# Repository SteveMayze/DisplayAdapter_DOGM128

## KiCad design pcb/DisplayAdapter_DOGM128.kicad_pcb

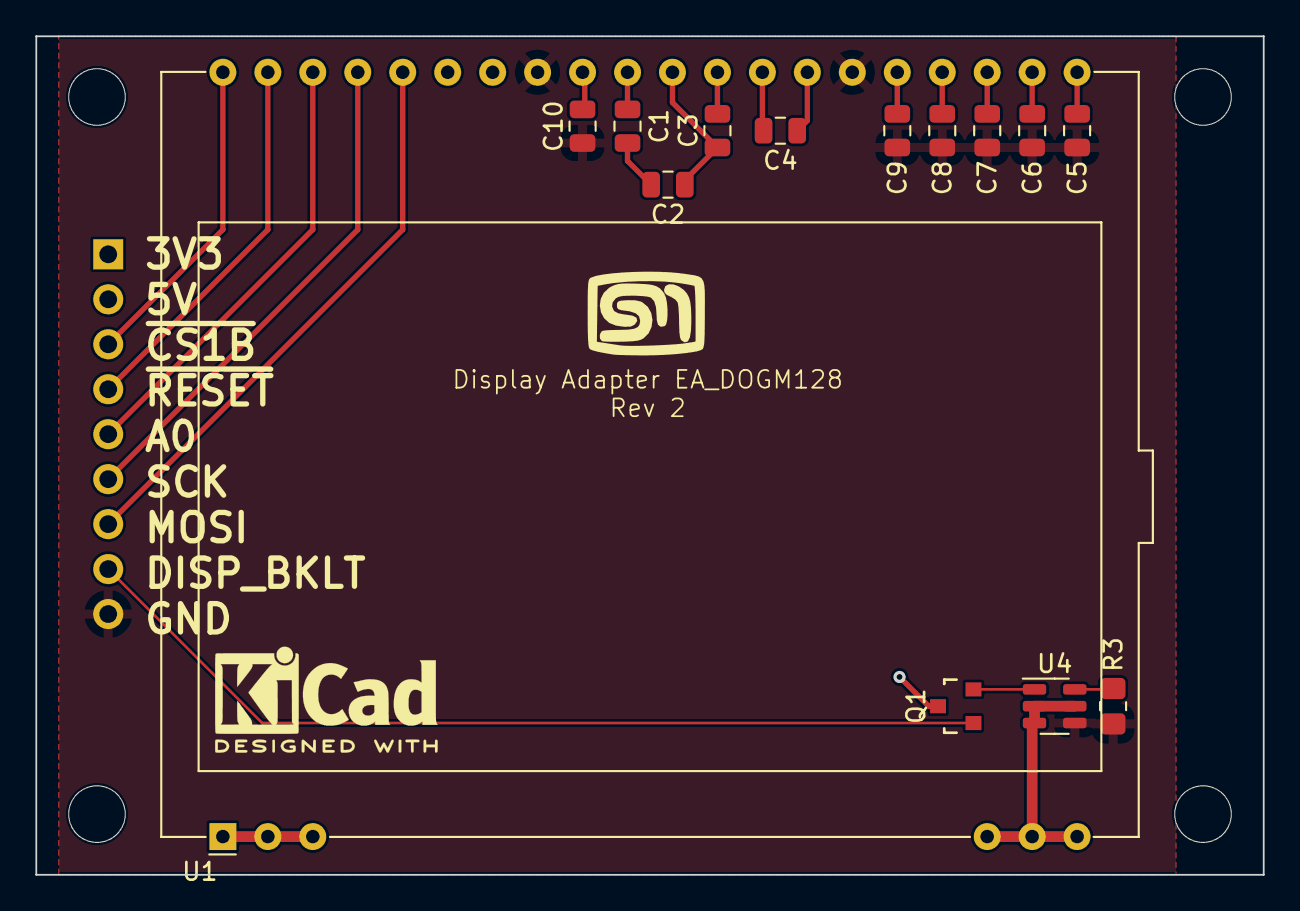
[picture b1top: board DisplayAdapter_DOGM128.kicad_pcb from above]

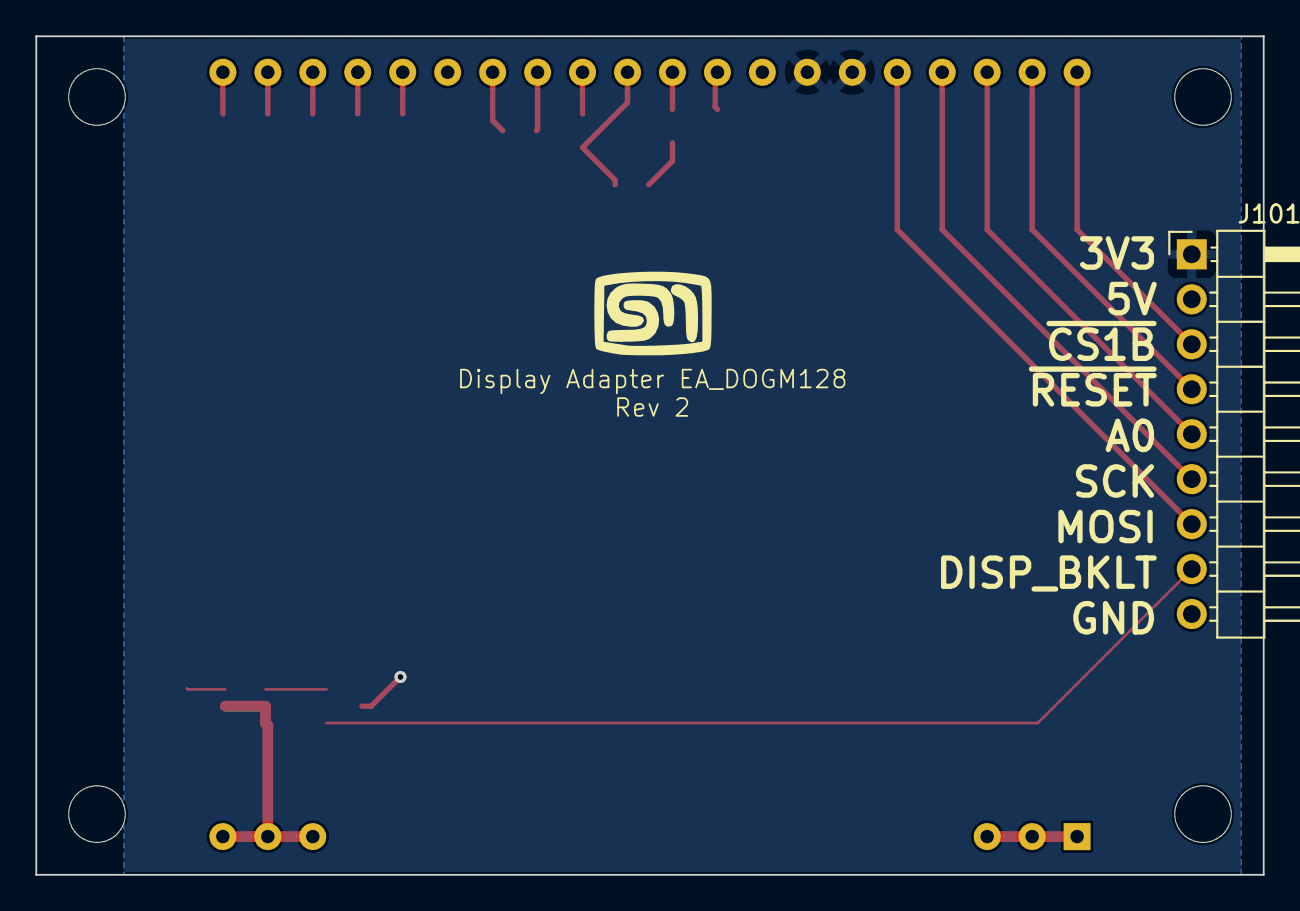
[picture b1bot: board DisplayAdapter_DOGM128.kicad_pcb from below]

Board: 2 copper layers, 69.3 x 47.4 mm, 22 parts (2 on the bottom side), 24 nets.

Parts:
C1, C2, C3, C4, C5, C6, C7, C8, C9, C10: 1μF; C_0805_2012Metric
H?: MountingHole; MountingHole_3.2mm_M3
H?#2, H?#3, H?#4: MountingHole; MountingHole_3.2mm_M3
J101: Conn_01x09_Male; PinHeader_1x09_P2.54mm_Horizontal
Lg?: logo; MyBasic_rounded_50_1
Lg?#2: logo; KiCad-Logo2_5mm_SilkScreen
Lg?#3: logo; MyBasic_rounded_50_1
Q1: IRLML2502; Micro3
R3: 80Ω; R_0805_2012Metric_Pad1.20x1.40mm_HandSolder
U4: BCR42XUW6; SOT-23-6
U?: EA_DOGM128X-6; EA_DOGM128-6

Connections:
/3V3: J101.1, Q1.3 (D), U?.34 (VDD2), U?.35 (VDD)
/A0: J101.5, U?.38 (A0)
/DISP_BKLT: J101.8, Q1.1 (G)
/MOSI: J101.7, U?.36 (SI)
/SCK: J101.6, U?.37 (SCL)
/~DISP_CS: J101.3, U?.40 (~CS1B)
/~DISP_REST: J101.4, U?.39 (~RST)
GND: C5.2, C6.2, C7.2, C8.2, C9.2, C10.2, J101.9, R3.2, U4.4 (GND), U?.26 (VSS), U?.33 (VSS)
unnamed: C1.1, C2.2
unnamed: C1.2, U?.31 (CAP3P)
unnamed: C2.1, C3.2, U?.30 (CAP1N)
unnamed: C3.1, U?.29 (CAP1P)
unnamed: C4.1, U?.27 (CAP2N)
unnamed: C4.2, U?.28 (CAP2P)
unnamed: C5.1, U?.21 (V0)
unnamed: C6.1, U?.22 (V1)
unnamed: C7.1, U?.23 (V2)
unnamed: C8.1, U?.24 (V3)
unnamed: C9.1, U?.25 (V4)
unnamed: C10.1, U?.32 (VOUT)
unnamed: Q1.2 (S), U4.1 (EN)
unnamed: R3.1, U4.6 (R_{ext})
unnamed: U?.1 (A1+), U?.2 (A2+), U?.3 (A3+)
unnamed: U4.2 (OUT), U4.3 (OUT), U4.5 (OUT), U?.18 (C1-), U?.19 (C2-), U?.20 (C3-)

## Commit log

2022-05-27 Initial checkin
2022-08-30 Revision 2
